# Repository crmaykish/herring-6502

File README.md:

# Herring 6502

Herring is an 8-bit computer built around the 65C02 CPU. It is designed as a backplane system. The backplane board is passive, providing only power, a reset switch, and system bus headers.
The system bus is exposed as single-row 40-pin female headers using standard 0.1 inch pin pitch.

## Hardware

The memory map is set up in the following way:

1. 0x0000 - 0x7FFF: Low RAM (32K)
2. 0x8000 - 0xBFFF: Bankable RAM (16K pages)
3. 0xC000 - 0xDFFF: Memory-mapped I/O (8K)
4. 0xE000 - 0xFFFF: ROM (8K)

Individual component boards are connected to the backplane via the 40-pin system bus. Most of the pins on the bus come directly from the 65C02 plus a few for peripheral support. They are mapped from left to right in the following order:

1. VCC (5v regulated)
2. GND
3. D0
4. D1
5. D2
6. D3
7. D4
8. D5
9. D6
10. D7
11. A0
12. A1
13. A2
14. A3
15. A4
16. A5
17. A6
18. A7
19. A8
20. A9
21. A10
22. A11
23. A12
24. A13
25. A14
26. A15
27. RESB - Reset (Active low)
28. CLK - System clock
29. RWB - Read/write flag (Read = high, Write = low)
30. IRQB - Interrupt request (Active low)
31. DEC0 - Functions as the RAM write-enable pin
32. DEC1 - Peripheral enable
33. DEC2 - Peripheral enable
34. DEC3 - Peripheral enable
35. DEC4 - Peripheral enable
36. DEC5 - Peripheral enable
37. DEC6 - Peripheral enable
38. DEC7 - Peripheral enable
39. BE - Bus Enable (Active high)
40. GND

## Software

Herring currently runs a simple monitor program from ROM that provides the basic peek, poke, jump commands as well as memory clearing and memory dumping. This monitor also functions as a bootloader, allowing new firmware to be copied into RAM from a host PC via serial port. I use a simple program on the PC to transfer firmware: https://github.com/crmaykish/ctt in this way.

All firmware development is done in C and uses the cc65 set of tools.

## Further Reading

See https://hackaday.io/project/181802-herring-6502-computer for project logs and more details on the hardware.

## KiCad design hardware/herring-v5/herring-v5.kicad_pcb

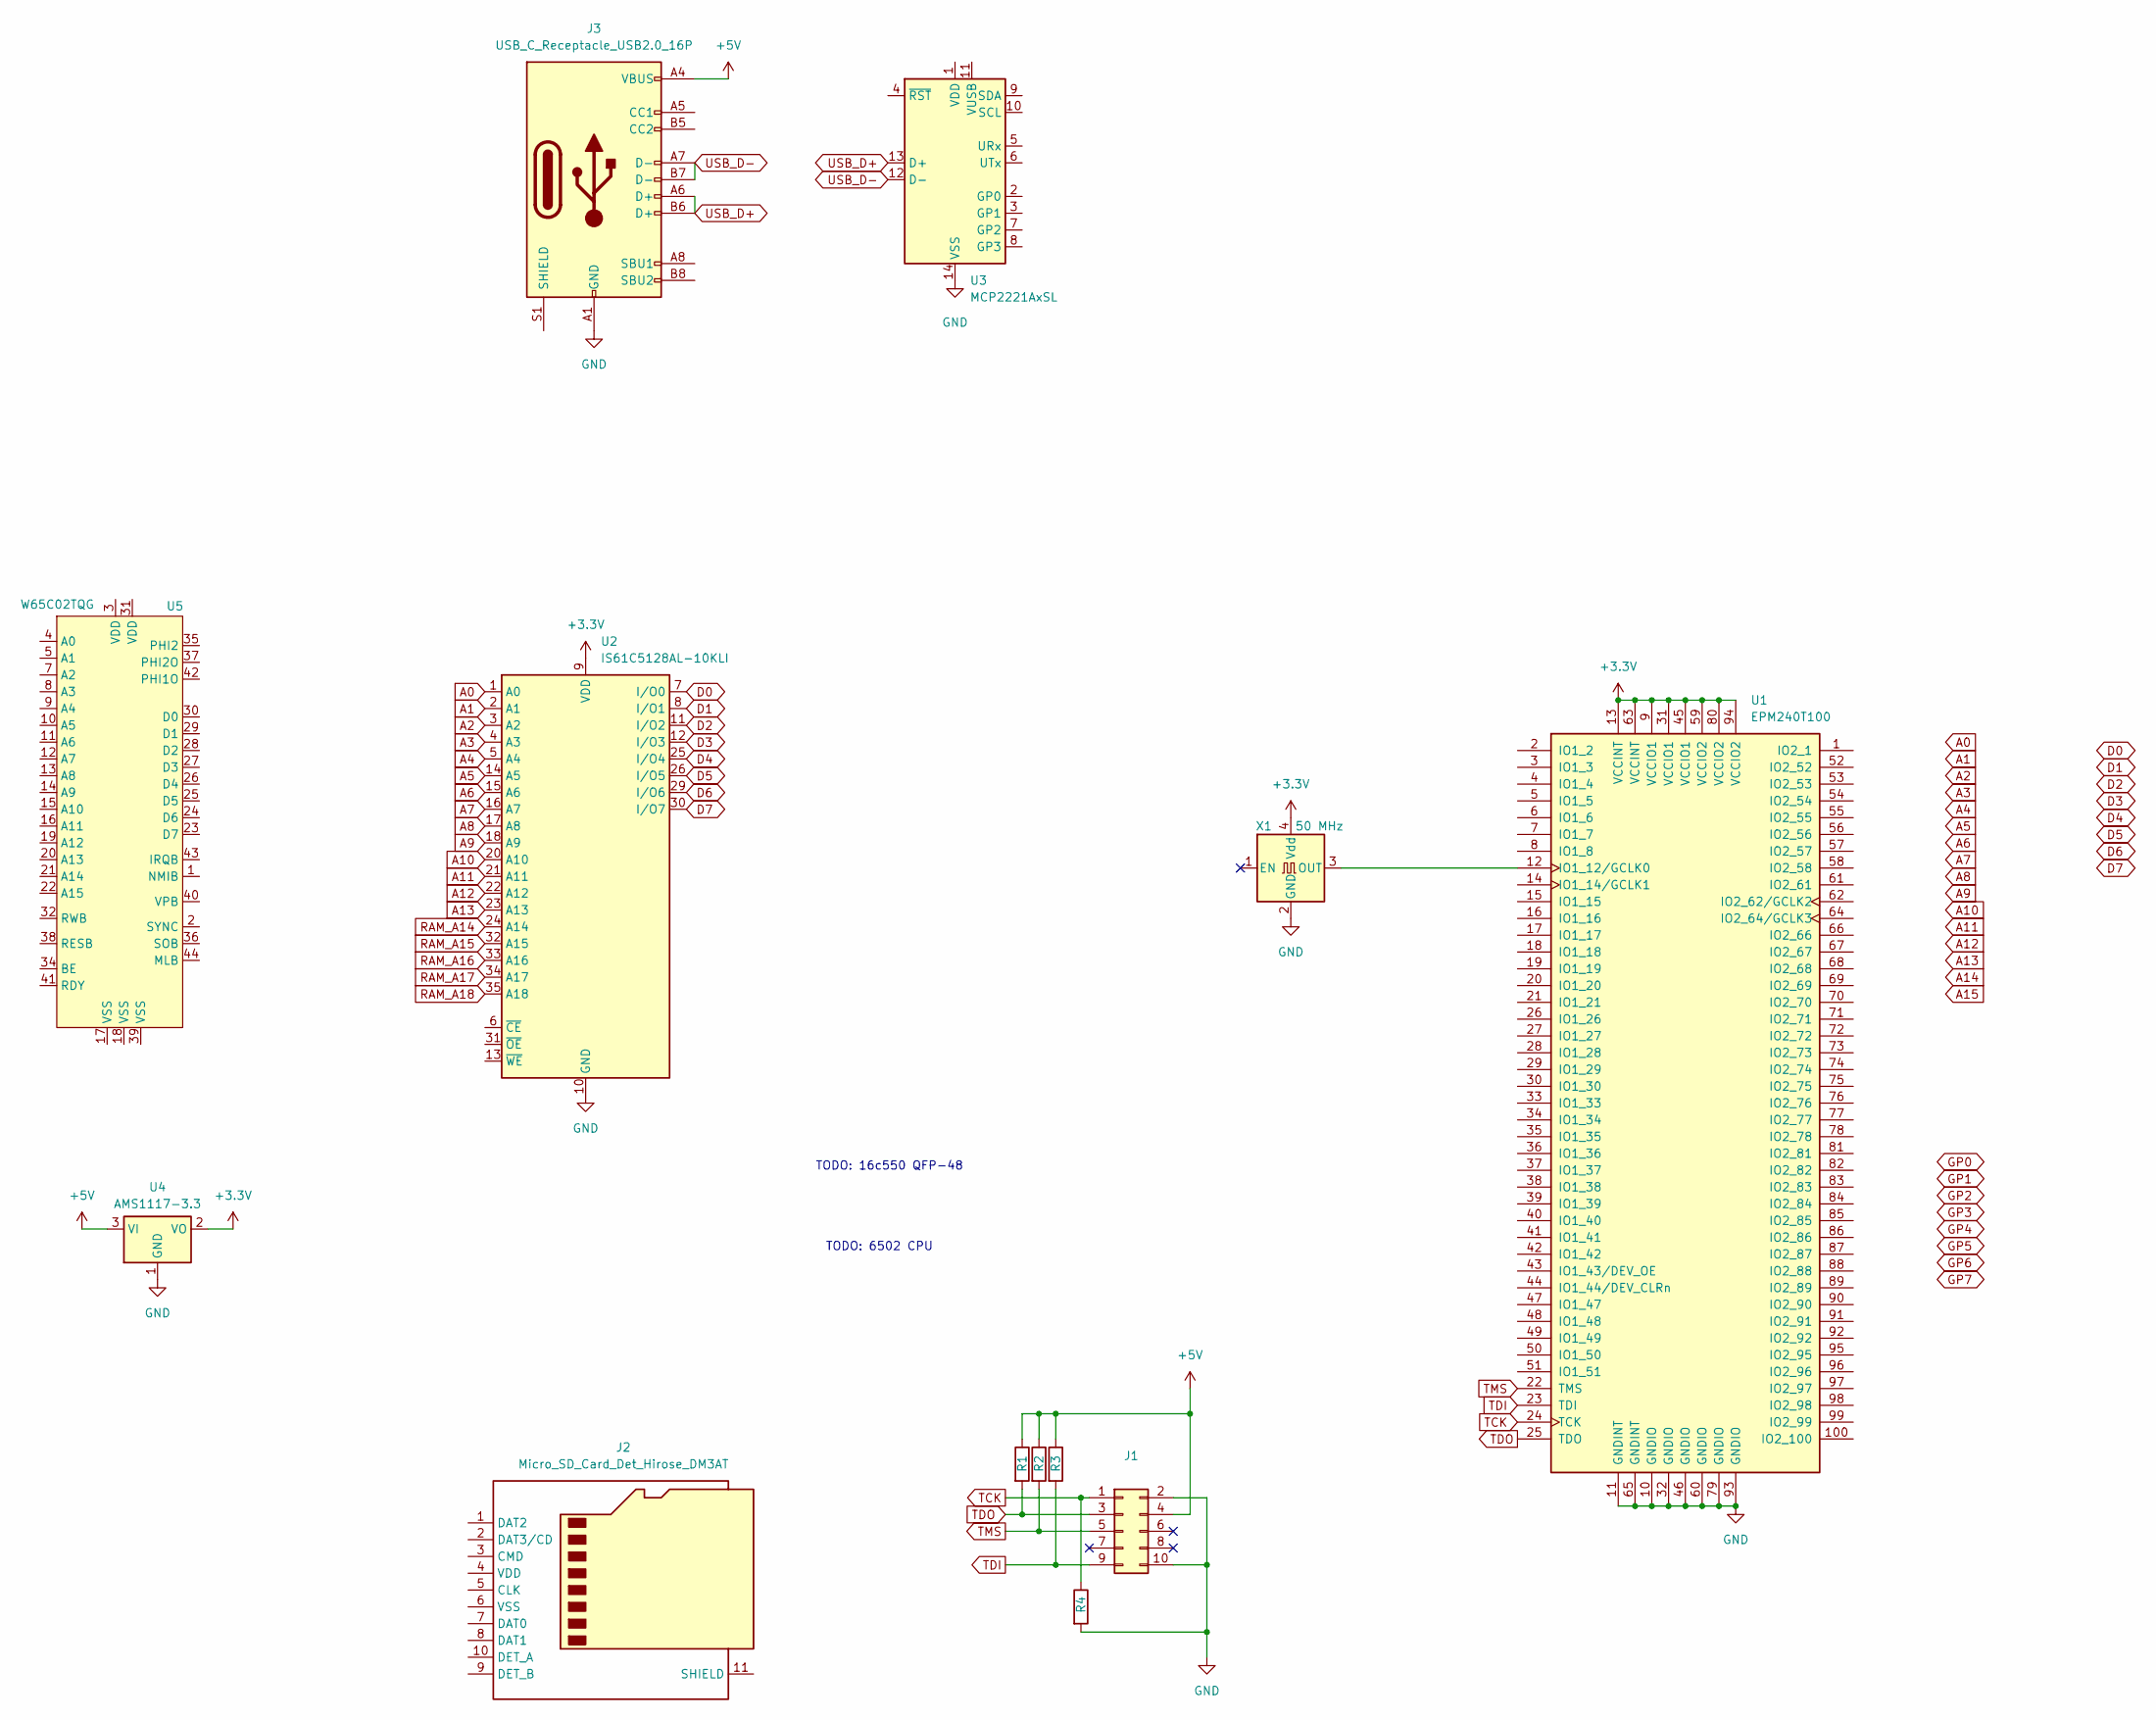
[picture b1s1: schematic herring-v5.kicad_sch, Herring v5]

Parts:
J1: Conn_02x05_Odd_Even; IDC-Header_2x05_P2.54mm_Vertical
J2: Micro_SD_Card_Det_Hirose_DM3AT; microSD_HC_Hirose_DM3AT-SF-PEJM5
J3: USB_C_Receptacle_USB2.0_16P; USB_C_Receptacle_GCT_USB4085
R1, R2, R3, R4: R; R_0805_2012Metric_Pad1.20x1.40mm_HandSolder
U1: EPM240T100; LQFP-100_14x14mm_P0.5mm
U2: IS61C5128AL-10KLI; SOJ-36_10.16x23.49mm_P1.27mm
U3: MCP2221AxSL; SOIC-14_3.9x8.7mm_P1.27mm
U4: AMS1117-3.3; SOT-223-3_TabPin2
U5: W65C02TQG; PQFP-44_10x10mm_P0.8mm
X1: 50 MHz; Oscillator_SMD_Abracon_ASV-4Pin_7.0x5.1mm

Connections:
+3.3V: U1.9 (VCCIO1), U1.13 (VCCINT), U1.31 (VCCIO1), U1.45 (VCCIO1), U1.59 (VCCIO2), U1.63 (VCCINT), U1.80 (VCCIO2), U1.94 (VCCIO2), U2.9 (VDD), U2.27 (VDD), U4.2 (VO), X1.4 (Vdd)
+5V: J1.4, J3.A4 (VBUS), J3.A9 (VBUS), J3.B4 (VBUS), J3.B9 (VBUS), R1.1, R2.1, R3.1, U4.3 (VI)
A0: U2.1 (A0)
A1: U2.2 (A1)
A2: U2.3 (A2)
A3: U2.4 (A3)
A4: U2.5 (A4)
A5: U2.14 (A5)
A6: U2.15 (A6)
A7: U2.16 (A7)
A8: U2.17 (A8)
A9: U2.18 (A9)
A10: U2.20 (A10)
A11: U2.21 (A11)
A12: U2.22 (A12)
A13: U2.23 (A13)
D0: U2.7 (I/O0)
D1: U2.8 (I/O1)
D2: U2.11 (I/O2)
D3: U2.12 (I/O3)
D4: U2.25 (I/O4)
D5: U2.26 (I/O5)
D6: U2.29 (I/O6)
D7: U2.30 (I/O7)
GND: J1.2, J1.10, J3.A1 (GND), J3.A12 (GND), J3.B1 (GND), J3.B12 (GND), R4.2, U1.10 (GNDIO), U1.11 (GNDINT), U1.32 (GNDIO), U1.46 (GNDIO), U1.60 (GNDIO), U1.65 (GNDINT), U1.79 (GNDIO), U1.93 (GNDIO), U2.10 (GND), U2.28 (GND), U3.14 (VSS), U4.1 (GND), X1.2 (GND)
unnamed: U1.12 (IO1_12/GCLK0), X1.3 (OUT)
RAM_A14: U2.24 (A14)
RAM_A15: U2.32 (A15)
RAM_A16: U2.33 (A16)
RAM_A17: U2.34 (A17)
RAM_A18: U2.35 (A18)
TCK: J1.1, R4.1, U1.24 (TCK)
TDI: J1.9, R3.2, U1.23 (TDI)
TDO: J1.3, R1.2, U1.25 (TDO)
TMS: J1.5, R2.2, U1.22 (TMS)
USB_D+: J3.A6 (D+), J3.B6 (D+), U3.13 (D+)
USB_D-: J3.A7 (D-), J3.B7 (D-), U3.12 (D-)

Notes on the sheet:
TODO: 16c550 QFP-48
TODO: 6502 CPU

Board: 2 copper layers, 13 parts (0 on the bottom side), 10 nets, no tracks yet.

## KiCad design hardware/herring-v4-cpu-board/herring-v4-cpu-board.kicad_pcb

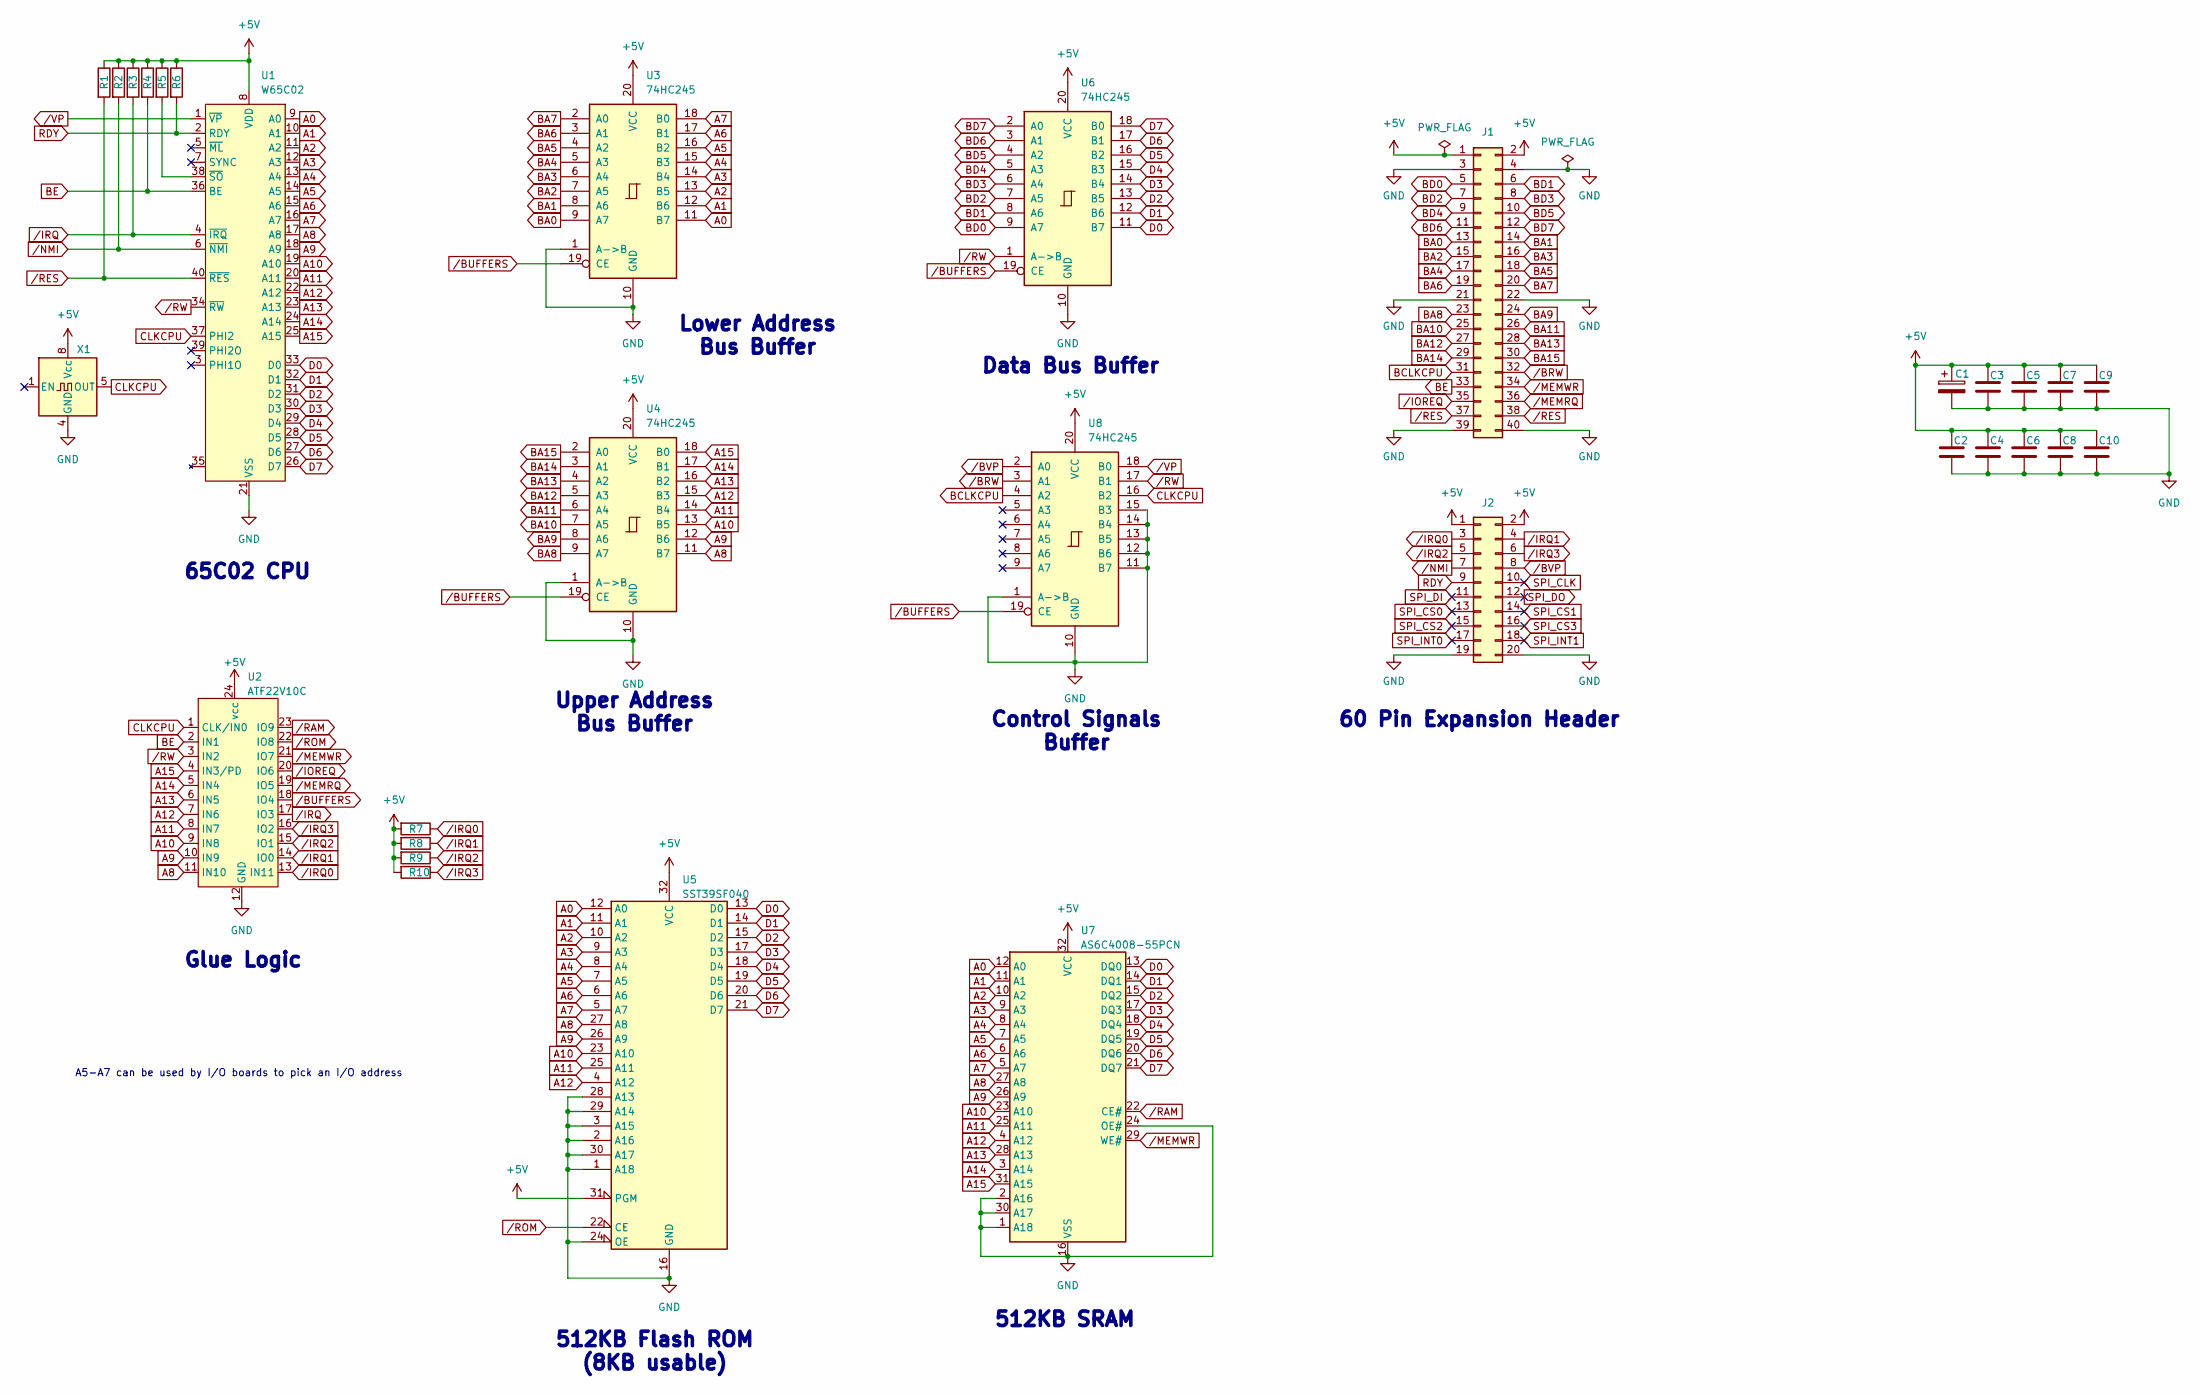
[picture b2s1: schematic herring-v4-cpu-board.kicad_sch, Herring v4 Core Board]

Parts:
C1: C_Polarized; CP_Radial_D10.0mm_P3.80mm
C2, C3, C4, C5, C6, C7, C8, C9, C10: C; C_Disc_D5.0mm_W2.5mm_P5.00mm
J1: Conn_02x20_Odd_Even; PinSocket_2x20_P2.54mm_Vertical
J2: Conn_02x10_Odd_Even; PinSocket_2x10_P2.54mm_Vertical
R1, R2, R3, R4, R5, R6, R7, R8, R9, R10: R; R_Axial_DIN0207_L6.3mm_D2.5mm_P7.62mm_Horizontal
U1: W65C02; DIP-40_W15.24mm
U2: ATF22V10C; DIP-24_W7.62mm
U3, U4, U6, U8: 74HC245; DIP-20_W7.62mm
U5: SST39SF040; DIP_Socket-32_W11.9_W12.7_W15.24_W17.78_W18.5_3M_232-1285-0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
U7: AS6C4008-55PCN; DIP-32_W15.24mm
X1: CXO_DIP8; Oscillator_DIP-8

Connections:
+5V: C1.1, C2.1, C3.1, C4.1, C5.1, C6.1, C7.1, C8.1, C9.1, C10.1, J1.1, J1.2, J2.1, J2.2, R1.1, R2.1, R3.1, R4.1, R5.1, R6.1, R7.2, R8.2, R9.2, R10.2, U1.8 (VDD), U2.24 (vcc), U3.20 (VCC), U4.20 (VCC), U5.31 (PGM), U5.32 (VCC), U6.20 (VCC), U7.32 (VCC), U8.20 (VCC), X1.8 (Vcc)
A0: U1.9 (A0), U3.11 (B7), U5.12 (A0), U7.12 (A0)
A1: U1.10 (A1), U3.12 (B6), U5.11 (A1), U7.11 (A1)
A2: U1.11 (A2), U3.13 (B5), U5.10 (A2), U7.10 (A2)
A3: U1.12 (A3), U3.14 (B4), U5.9 (A3), U7.9 (A3)
A4: U1.13 (A4), U3.15 (B3), U5.8 (A4), U7.8 (A4)
A5: U1.14 (A5), U3.16 (B2), U5.7 (A5), U7.7 (A5)
A6: U1.15 (A6), U3.17 (B1), U5.6 (A6), U7.6 (A6)
A7: U1.16 (A7), U3.18 (B0), U5.5 (A7), U7.5 (A7)
A8: U1.17 (A8), U2.11 (IN10), U4.11 (B7), U5.27 (A8), U7.27 (A8)
A9: U1.18 (A9), U2.10 (IN9), U4.12 (B6), U5.26 (A9), U7.26 (A9)
A10: U1.19 (A10), U2.9 (IN8), U4.13 (B5), U5.23 (A10), U7.23 (A10)
A11: U1.20 (A11), U2.8 (IN7), U4.14 (B4), U5.25 (A11), U7.25 (A11)
A12: U1.22 (A12), U2.7 (IN6), U4.15 (B3), U5.4 (A12), U7.4 (A12)
A13: U1.23 (A13), U2.6 (IN5), U4.16 (B2), U7.28 (A13)
A14: U1.24 (A14), U2.5 (IN4), U4.17 (B1), U7.3 (A14)
A15: U1.25 (A15), U2.4 (IN3/PD), U4.18 (B0), U7.31 (A15)
BA0: J1.13, U3.9 (A7)
BA1: J1.14, U3.8 (A6)
BA2: J1.15, U3.7 (A5)
BA3: J1.16, U3.6 (A4)
BA4: J1.17, U3.5 (A3)
BA5: J1.18, U3.4 (A2)
BA6: J1.19, U3.3 (A1)
BA7: J1.20, U3.2 (A0)
BA8: J1.23, U4.9 (A7)
BA9: J1.24, U4.8 (A6)
BA10: J1.25, U4.7 (A5)
BA11: J1.26, U4.6 (A4)
BA12: J1.27, U4.5 (A3)
BA13: J1.28, U4.4 (A2)
BA14: J1.29, U4.3 (A1)
BA15: J1.30, U4.2 (A0)
BCLKCPU: J1.31, U8.4 (A2)
BD0: J1.5, U6.9 (A7)
BD1: J1.6, U6.8 (A6)
BD2: J1.7, U6.7 (A5)
BD3: J1.8, U6.6 (A4)
BD4: J1.9, U6.5 (A3)
BD5: J1.10, U6.4 (A2)
BD6: J1.11, U6.3 (A1)
BD7: J1.12, U6.2 (A0)
BE: J1.33, R4.2, U1.36 (BE), U2.2 (IN1)
CLKCPU: U1.37 (PHI2), U2.1 (CLK/IN0), U8.16 (B2), X1.5 (OUT)
D0: U1.33 (D0), U5.13 (D0), U6.11 (B7), U7.13 (DQ0)
D1: U1.32 (D1), U5.14 (D1), U6.12 (B6), U7.14 (DQ1)
D2: U1.31 (D2), U5.15 (D2), U6.13 (B5), U7.15 (DQ2)
D3: U1.30 (D3), U5.17 (D3), U6.14 (B4), U7.17 (DQ3)
D4: U1.29 (D4), U5.18 (D4), U6.15 (B3), U7.18 (DQ4)
D5: U1.28 (D5), U5.19 (D5), U6.16 (B2), U7.19 (DQ5)
D6: U1.27 (D6), U5.20 (D6), U6.17 (B1), U7.20 (DQ6)
D7: U1.26 (D7), U5.21 (D7), U6.18 (B0), U7.21 (DQ7)
GND: C1.2, C2.2, C3.2, C4.2, C5.2, C6.2, C7.2, C8.2, C9.2, C10.2, J1.3, J1.4, J1.21, J1.22, J1.39, J1.40, J2.19, J2.20, U1.21 (VSS), U2.12 (GND), U3.1 (A->B), U3.10 (GND), U4.1 (A->B), U4.10 (GND), U5.1 (A18), U5.2 (A16), U5.3 (A15), U5.16 (GND), U5.24 (OE), U5.28 (A13), U5.29 (A14), U5.30 (A17), U6.10 (GND), U7.1 (A18), U7.2 (A16), U7.16 (VSS), U7.24 (OE#), U7.30 (A17), U8.1 (A->B), U8.10 (GND), U8.11 (B7), U8.12 (B6), U8.13 (B5), U8.14 (B4), U8.15 (B3), X1.4 (GND)
unnamed: R5.2, U1.38 (~SO)
RDY: J2.9, R6.2, U1.2 (RDY)
SPI_CLK: J2.10
SPI_CS0: J2.13
SPI_CS1: J2.14
SPI_CS2: J2.15
SPI_CS3: J2.16
SPI_DI: J2.11
SPI_DO: J2.12
SPI_INT0: J2.17
SPI_INT1: J2.18
/BRW: J1.32, U8.3 (A1)
/BUFFERS: U2.18 (IO4), U3.19 (CE), U4.19 (CE), U6.19 (CE), U8.19 (CE)
/BVP: J2.8, U8.2 (A0)
/IOREQ: J1.35, U2.20 (IO6)
/IRQ: R3.2, U1.4 (~IRQ), U2.17 (IO3)
/IRQ0: J2.3, R7.1, U2.13 (IN11)
/IRQ1: J2.4, R8.1, U2.14 (IO0)
/IRQ2: J2.5, R9.1, U2.15 (IO1)
/IRQ3: J2.6, R10.1, U2.16 (IO2)
/MEMRQ: J1.36, U2.19 (IO5)
/MEMWR: J1.34, U2.21 (IO7), U7.29 (WE#)
/NMI: J2.7, R2.2, U1.6 (~NMI)
/RAM: U2.23 (IO9), U7.22 (CE#)
/RES: J1.37, J1.38, R1.2, U1.40 (~RES)
/ROM: U2.22 (IO8), U5.22 (CE)
/RW: U1.34 (~RW), U2.3 (IN2), U6.1 (A->B), U8.17 (B1)
/VP: U1.1 (~VP), U8.18 (B0)

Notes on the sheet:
65C02 CPU
A5-A7 can be used by I/O boards to pick an I/O address
Glue Logic
Upper Address Bus Buffer
Control Signals Buffer
512KB SRAM
Lower Address Bus Buffer
512KB Flash ROM (8KB usable)
Data Bus Buffer
60 Pin Expansion Header

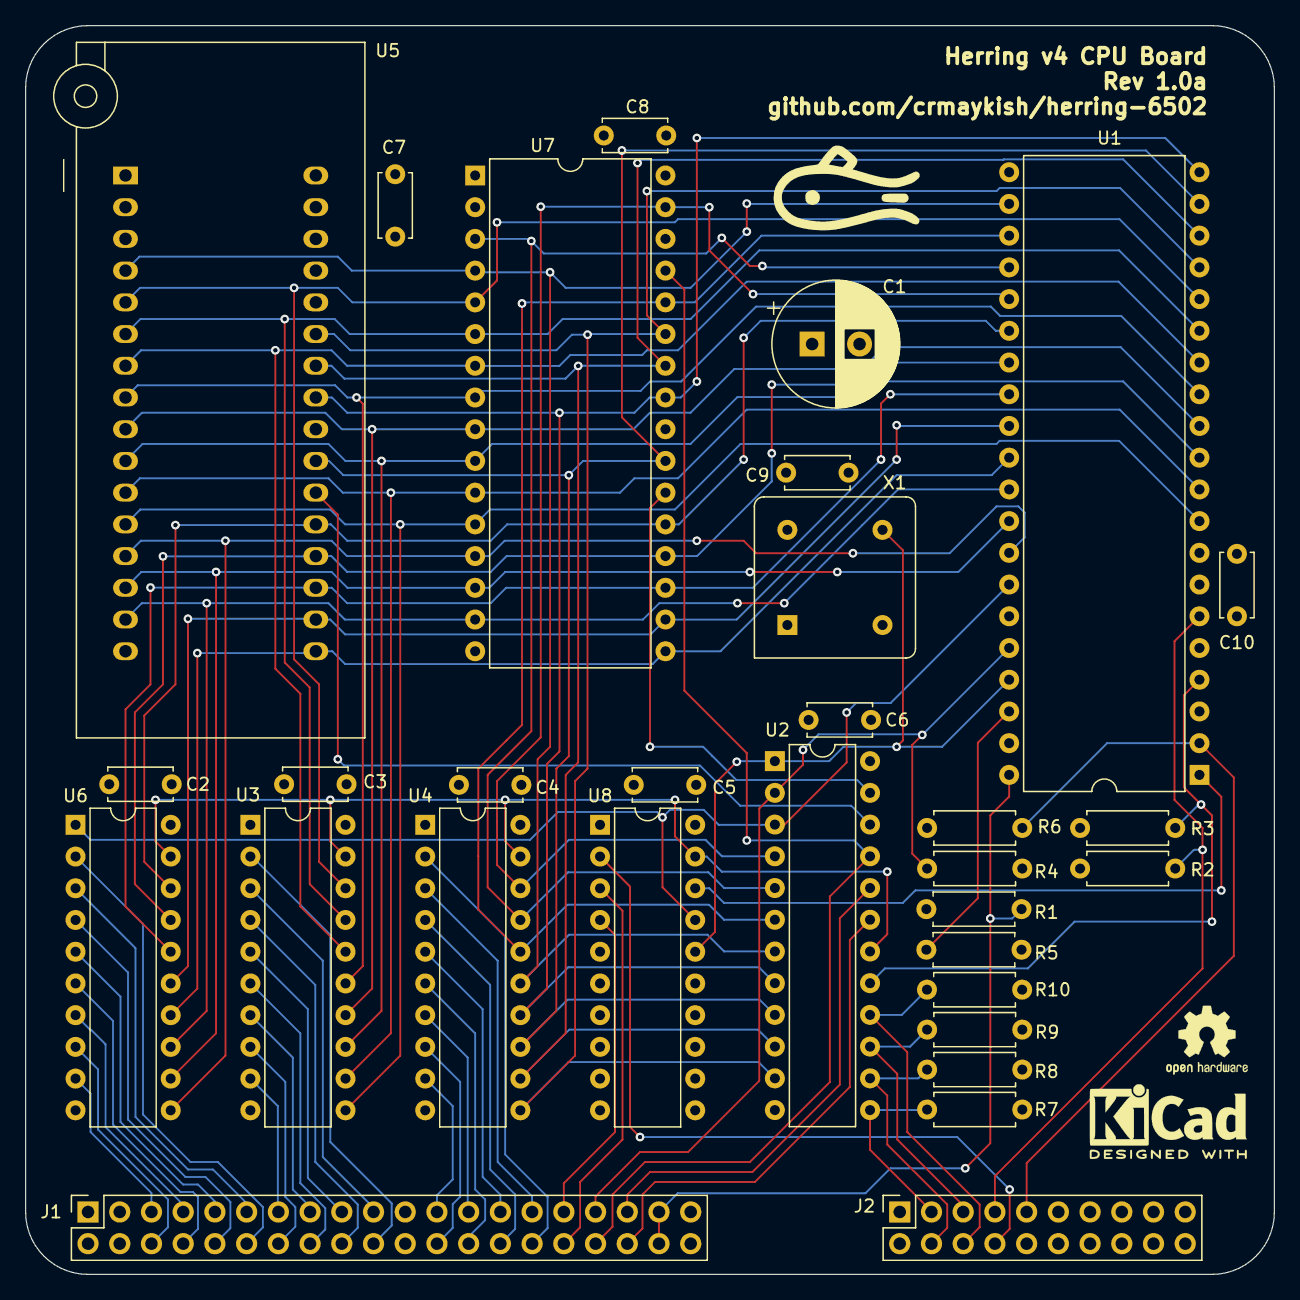
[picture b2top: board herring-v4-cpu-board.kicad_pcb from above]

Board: 4 copper layers, 100.0 x 100.0 mm, 31 parts (0 on the bottom side), 72 nets.

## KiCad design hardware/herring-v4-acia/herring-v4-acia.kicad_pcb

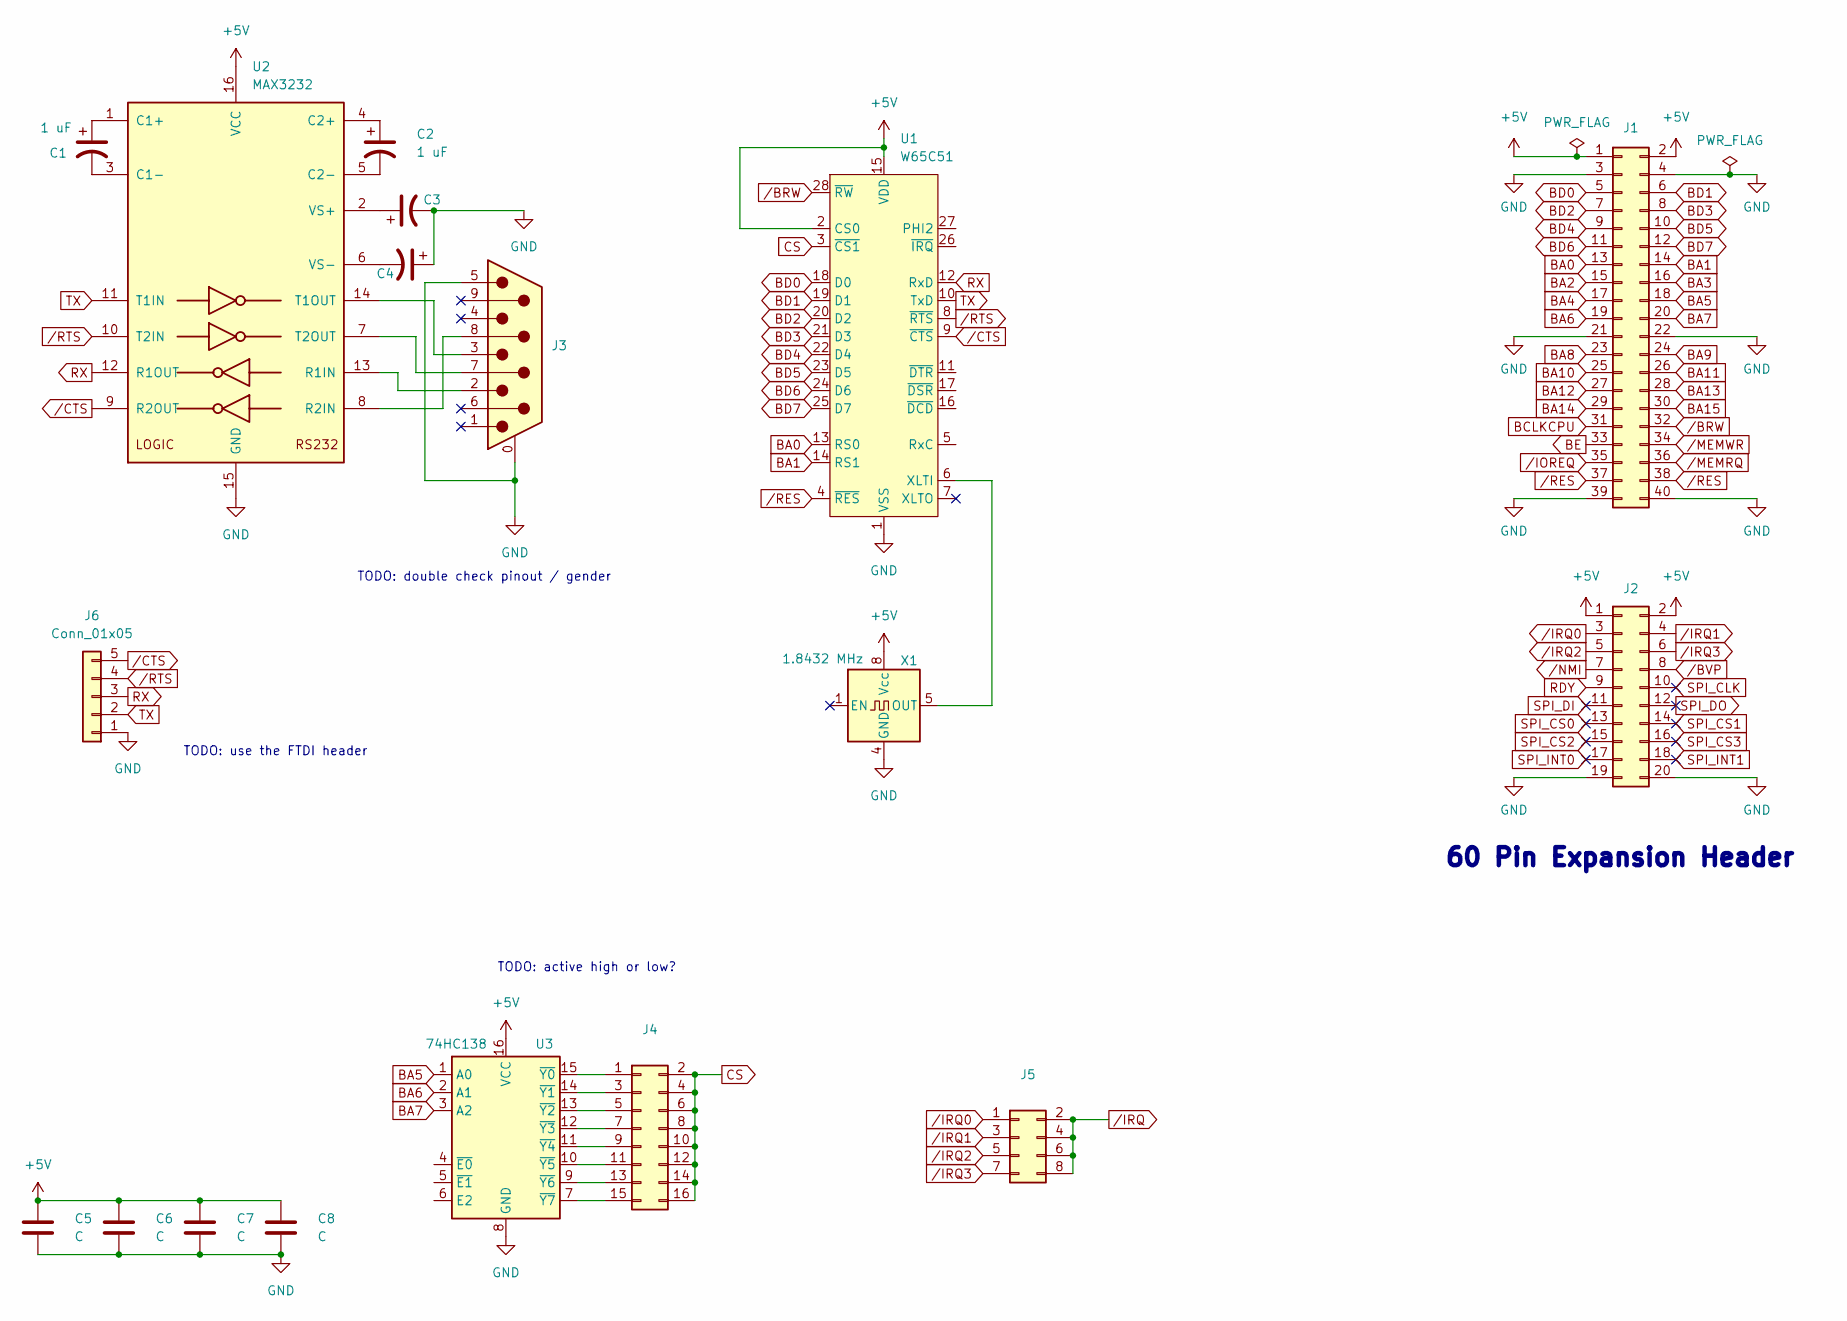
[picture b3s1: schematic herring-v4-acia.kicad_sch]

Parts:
C1, C2, C3: 1 uF; CP_Radial_D5.0mm_P2.50mm
C4: C_Polarized_US; CP_Radial_D5.0mm_P2.50mm
C5, C6, C7, C8: C; C_Disc_D4.3mm_W1.9mm_P5.00mm
J1: Conn_02x20_Odd_Even; PinSocket_2x20_P2.54mm_Vertical
J2: Conn_02x10_Odd_Even; PinSocket_2x10_P2.54mm_Vertical
J3: DE9_Plug_MountingHoles; DSUB-9_Male_Horizontal_P2.77x2.84mm_EdgePinOffset7.70mm_Hou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
J4: Conn_02x08_Odd_Even; PinHeader_2x08_P2.54mm_Vertical
J5: Conn_02x04_Odd_Even; PinHeader_2x04_P2.54mm_Vertical
J6: Conn_01x05; PinHeader_1x05_P2.54mm_Horizontal
U1: W65C51; DIP-28_W15.24mm
U2: MAX3232; DIP-16_W7.62mm
U3: 74HC138; DIP-16_W7.62mm
X1: 1.8432 MHz; Oscillator_DIP-8

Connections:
+5V: C5.1, C6.1, C7.1, C8.1, J1.1, J1.2, J2.1, J2.2, U1.2 (CS0), U1.15 (VDD), U2.16 (VCC), U3.16 (VCC), X1.8 (Vcc)
BA0: J1.13, U1.13 (RS0)
BA1: J1.14, U1.14 (RS1)
BA2: J1.15
BA3: J1.16
BA4: J1.17
BA5: J1.18, U3.1 (A0)
BA6: J1.19, U3.2 (A1)
BA7: J1.20, U3.3 (A2)
BA8: J1.23
BA9: J1.24
BA10: J1.25
BA11: J1.26
BA12: J1.27
BA13: J1.28
BA14: J1.29
BA15: J1.30
BCLKCPU: J1.31
BD0: J1.5, U1.18 (D0)
BD1: J1.6, U1.19 (D1)
BD2: J1.7, U1.20 (D2)
BD3: J1.8, U1.21 (D3)
BD4: J1.9, U1.22 (D4)
BD5: J1.10, U1.23 (D5)
BD6: J1.11, U1.24 (D6)
BD7: J1.12, U1.25 (D7)
BE: J1.33
CS: J4.2, J4.4, J4.6, J4.8, J4.10, J4.12, J4.14, J4.16, U1.3 (~CS1)
GND: C3.2, C4.1, C5.2, C6.2, C7.2, C8.2, J1.3, J1.4, J1.21, J1.22, J1.39, J1.40, J2.19, J2.20, J3.0 (PAD), J3.5, J6.1, U1.1 (VSS), U2.15 (GND), U3.8 (GND), X1.4 (GND)
unnamed: J4.1, U3.15 (~Y0)
unnamed: J4.3, U3.14 (~Y1)
unnamed: J4.5, U3.13 (~Y2)
unnamed: J4.7, U3.12 (~Y3)
unnamed: J4.9, U3.11 (~Y4)
unnamed: J4.11, U3.10 (~Y5)
unnamed: J4.13, U3.9 (~Y6)
unnamed: J4.15, U3.7 (~Y7)
unnamed: U1.6 (XLTI), X1.5 (OUT)
unnamed: C1.1, U2.1 (C1+)
unnamed: C1.2, U2.3 (C1-)
unnamed: C2.1, U2.4 (C2+)
unnamed: C2.2, U2.5 (C2-)
unnamed: J3.2, U2.13 (R1IN)
unnamed: J3.8, U2.8 (R2IN)
unnamed: J3.3, U2.14 (T1OUT)
unnamed: J3.7, U2.7 (T2OUT)
unnamed: C3.1, U2.2 (VS+)
unnamed: C4.2, U2.6 (VS-)
RDY: J2.9
RX: J6.3, U1.12 (RxD), U2.12 (R1OUT)
SPI_CLK: J2.10
SPI_CS0: J2.13
SPI_CS1: J2.14
SPI_CS2: J2.15
SPI_CS3: J2.16
SPI_DI: J2.11
SPI_DO: J2.12
SPI_INT0: J2.17
SPI_INT1: J2.18
TX: J6.2, U1.10 (TxD), U2.11 (T1IN)
/BRW: J1.32, U1.28 (~RW)
/BVP: J2.8
/CTS: J6.5, U1.9 (~CTS), U2.9 (R2OUT)
/IOREQ: J1.35
/IRQ: J5.2, J5.4, J5.6, J5.8
/IRQ0: J2.3, J5.1
/IRQ1: J2.4, J5.3
/IRQ2: J2.5, J5.5
/IRQ3: J2.6, J5.7
/MEMRQ: J1.36
/MEMWR: J1.34
/NMI: J2.7
/RES: J1.37, J1.38, U1.4 (~RES)
/RTS: J6.4, U1.8 (~RTS), U2.10 (T2IN)

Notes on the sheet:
TODO: use the FTDI header
TODO: active high or low?
TODO: double check pinout / gender
60 Pin Expansion Header

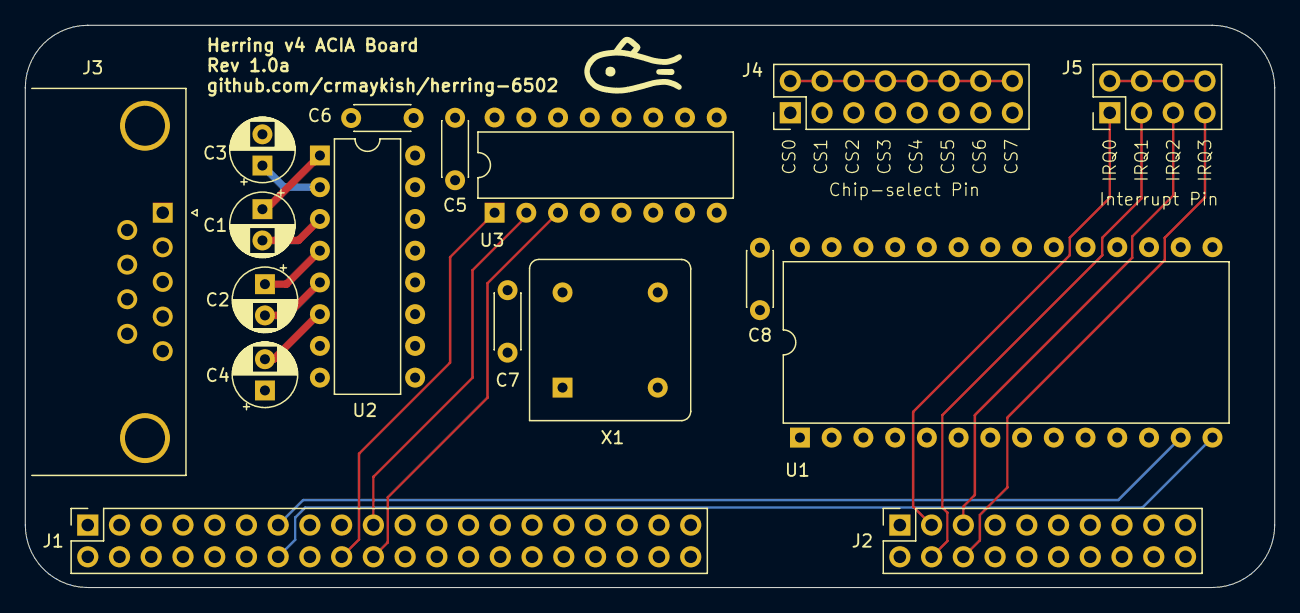
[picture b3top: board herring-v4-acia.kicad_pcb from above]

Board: 2 copper layers, 100.0 x 45.0 mm, 17 parts (0 on the bottom side), 46 nets.

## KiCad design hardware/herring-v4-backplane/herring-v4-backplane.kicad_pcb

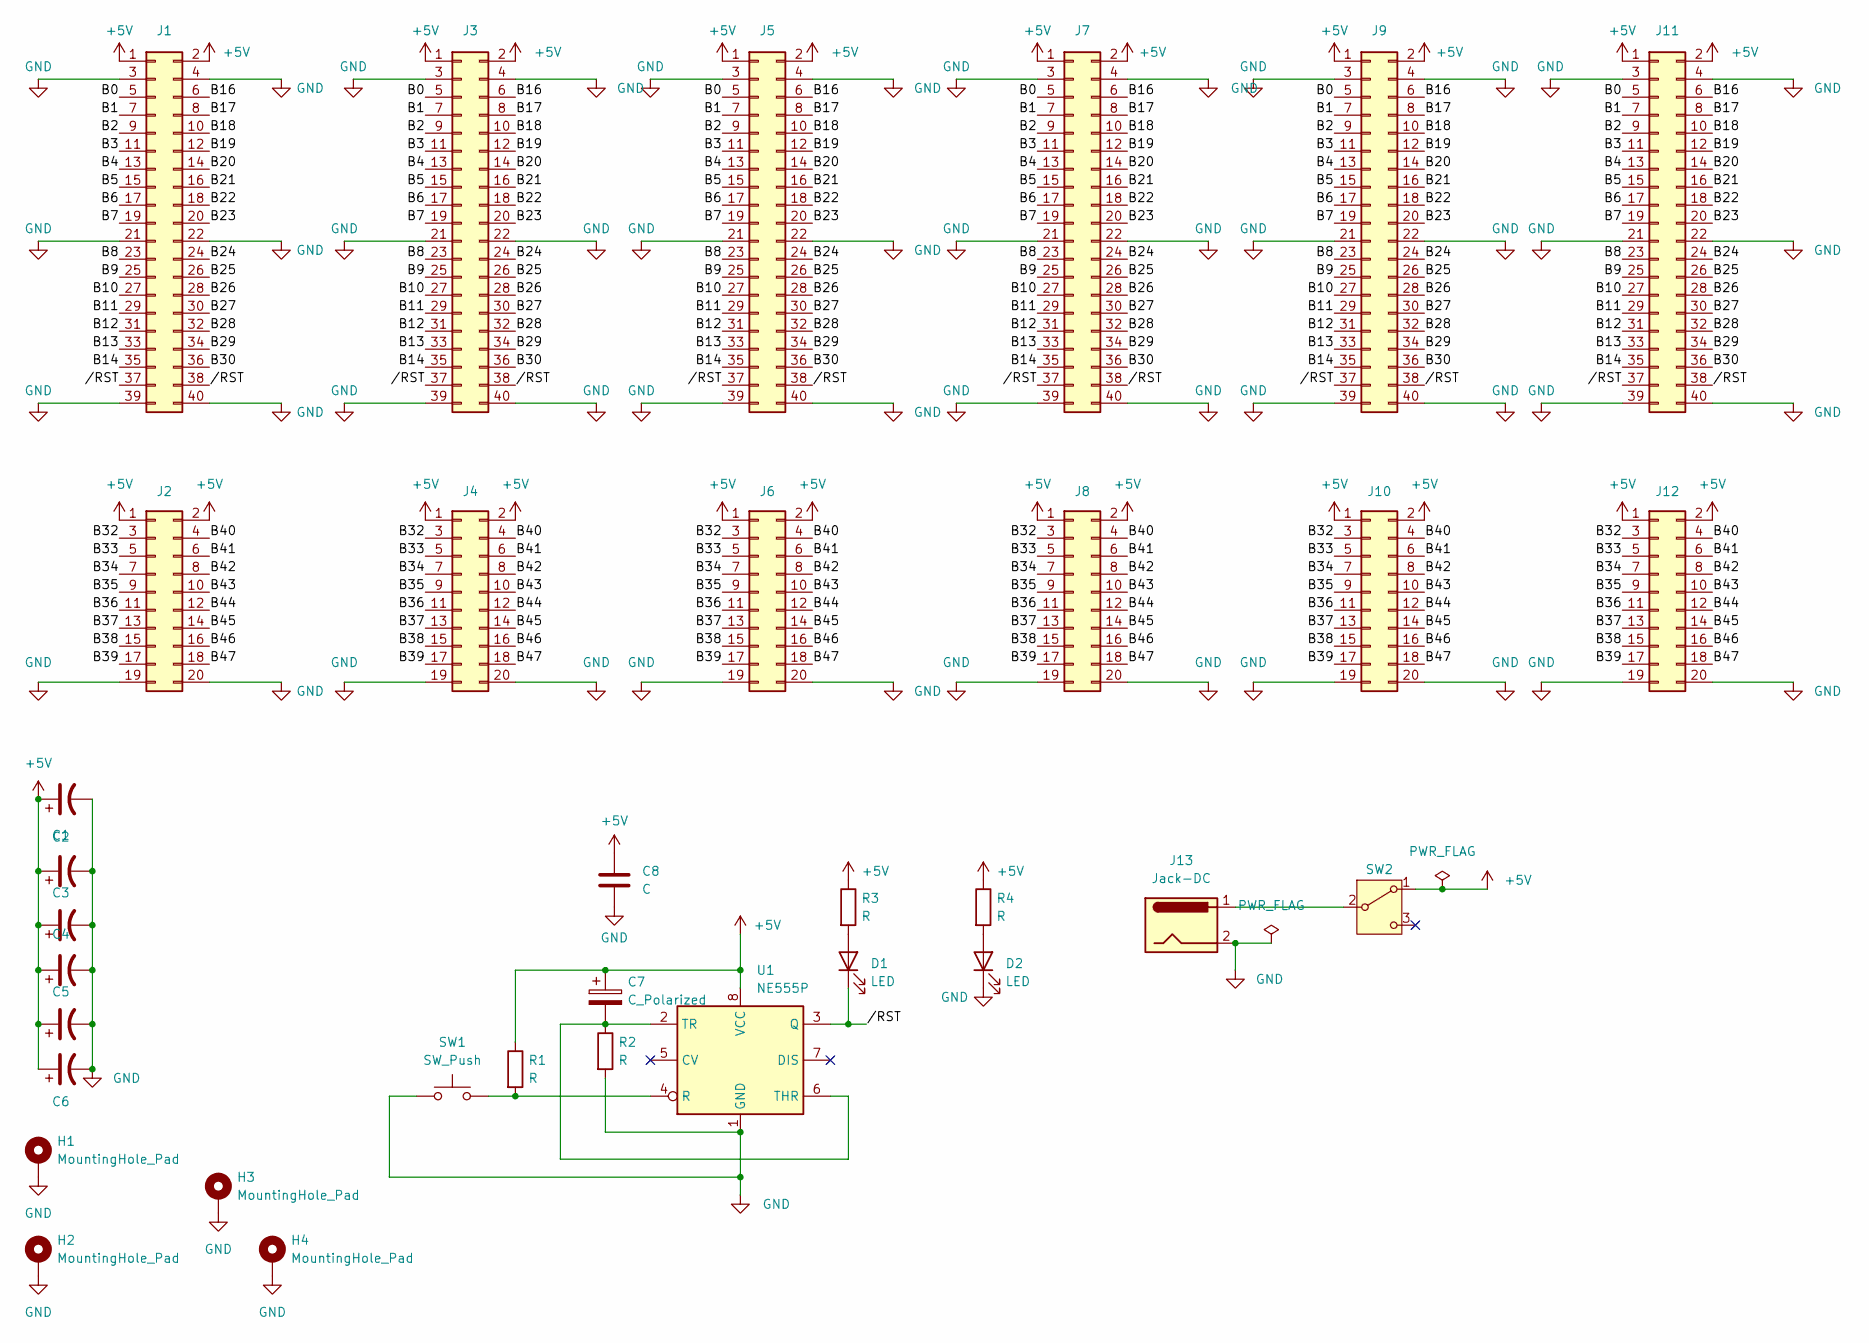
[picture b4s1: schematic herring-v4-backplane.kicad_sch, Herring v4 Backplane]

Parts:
C1: C_Polarized_US; CP_Radial_D8.0mm_P3.80mm
C2, C3, C4, C5, C6: C_Polarized_US; CP_Radial_D5.0mm_P2.50mm
C7: C_Polarized; CP_Radial_D5.0mm_P2.50mm
C8: C; C_Disc_D4.3mm_W1.9mm_P5.00mm
D1, D2: LED; LED_D5.0mm
H1, H2, H3, H4: MountingHole_Pad; MountingHole_3.2mm_M3_Pad
J1, J3, J5, J7, J9, J11: Conn_02x20_Odd_Even; PinSocket_2x20_P2.54mm_Vertical
J2, J4, J6, J8, J10, J12: Conn_02x10_Odd_Even; PinSocket_2x10_P2.54mm_Vertical
J13: Jack-DC; BarrelJack_Kycon_KLDX-0202-xC_Horizontal
R1, R2, R3, R4: R; R_Axial_DIN0207_L6.3mm_D2.5mm_P7.62mm_Horizontal
SW1: SW_Push; SW_PUSH_6mm_H5mm
SW2: SW_SPDT; SW_Mini_Toggle
U1: NE555P; DIP-8_W7.62mm

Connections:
+5V: C1.1, C2.1, C3.1, C4.1, C5.1, C6.1, C7.1, C8.1, J1.1, J1.2, J2.1, J2.2, J3.1, J3.2, J4.1, J4.2, J5.1, J5.2, J6.1, J6.2, J7.1, J7.2, J8.1, J8.2, J9.1, J9.2, J10.1, J10.2, J11.1, J11.2, J12.1, J12.2, R1.1, R3.1, R4.1, SW2.1 (A), U1.8 (VCC)
/B0: J1.5, J3.5, J5.5, J7.5, J9.5, J11.5
/B1: J1.7, J3.7, J5.7, J7.7, J9.7, J11.7
/B2: J1.9, J3.9, J5.9, J7.9, J9.9, J11.9
/B3: J1.11, J3.11, J5.11, J7.11, J9.11, J11.11
/B4: J1.13, J3.13, J5.13, J7.13, J9.13, J11.13
/B5: J1.15, J3.15, J5.15, J7.15, J9.15, J11.15
/B6: J1.17, J3.17, J5.17, J7.17, J9.17, J11.17
/B7: J1.19, J3.19, J5.19, J7.19, J9.19, J11.19
/B8: J1.23, J3.23, J5.23, J7.23, J9.23, J11.23
/B9: J1.25, J3.25, J5.25, J7.25, J9.25, J11.25
/B10: J1.27, J3.27, J5.27, J7.27, J9.27, J11.27
/B11: J1.29, J3.29, J5.29, J7.29, J9.29, J11.29
/B12: J1.31, J3.31, J5.31, J7.31, J9.31, J11.31
/B13: J1.33, J3.33, J5.33, J7.33, J9.33, J11.33
/B14: J1.35, J3.35, J5.35, J7.35, J9.35, J11.35
/B16: J1.6, J3.6, J5.6, J7.6, J9.6, J11.6
/B17: J1.8, J3.8, J5.8, J7.8, J9.8, J11.8
/B18: J1.10, J3.10, J5.10, J7.10, J9.10, J11.10
/B19: J1.12, J3.12, J5.12, J7.12, J9.12, J11.12
/B20: J1.14, J3.14, J5.14, J7.14, J9.14, J11.14
/B21: J1.16, J3.16, J5.16, J7.16, J9.16, J11.16
/B22: J1.18, J3.18, J5.18, J7.18, J9.18, J11.18
/B23: J1.20, J3.20, J5.20, J7.20, J9.20, J11.20
/B24: J1.24, J3.24, J5.24, J7.24, J9.24, J11.24
/B25: J1.26, J3.26, J5.26, J7.26, J9.26, J11.26
/B26: J1.28, J3.28, J5.28, J7.28, J9.28, J11.28
/B27: J1.30, J3.30, J5.30, J7.30, J9.30, J11.30
/B28: J1.32, J3.32, J5.32, J7.32, J9.32, J11.32
/B29: J1.34, J3.34, J5.34, J7.34, J9.34, J11.34
/B30: J1.36, J3.36, J5.36, J7.36, J9.36, J11.36
/B32: J2.3, J4.3, J6.3, J8.3, J10.3, J12.3
/B33: J2.5, J4.5, J6.5, J8.5, J10.5, J12.5
/B34: J2.7, J4.7, J6.7, J8.7, J10.7, J12.7
/B35: J2.9, J4.9, J6.9, J8.9, J10.9, J12.9
/B36: J2.11, J4.11, J6.11, J8.11, J10.11, J12.11
/B37: J2.13, J4.13, J6.13, J8.13, J10.13, J12.13
/B38: J2.15, J4.15, J6.15, J8.15, J10.15, J12.15
/B39: J2.17, J4.17, J6.17, J8.17, J10.17, J12.17
/B40: J2.4, J4.4, J6.4, J8.4, J10.4, J12.4
/B41: J2.6, J4.6, J6.6, J8.6, J10.6, J12.6
/B42: J2.8, J4.8, J6.8, J8.8, J10.8, J12.8
/B43: J2.10, J4.10, J6.10, J8.10, J10.10, J12.10
/B44: J2.12, J4.12, J6.12, J8.12, J10.12, J12.12
/B45: J2.14, J4.14, J6.14, J8.14, J10.14, J12.14
/B46: J2.16, J4.16, J6.16, J8.16, J10.16, J12.16
/B47: J2.18, J4.18, J6.18, J8.18, J10.18, J12.18
//RST: D1.1 (K), J1.37, J1.38, J3.37, J3.38, J5.37, J5.38, J7.37, J7.38, J9.37, J9.38, J11.37, J11.38, U1.3 (Q)
GND: C1.2, C2.2, C3.2, C4.2, C5.2, C6.2, C8.2, D2.1 (K), H1.1, H2.1, H3.1, H4.1, J1.3, J1.4, J1.21, J1.22, J1.39, J1.40, J2.19, J2.20, J3.3, J3.4, J3.21, J3.22, J3.39, J3.40, J4.19, J4.20, J5.3, J5.4, J5.21, J5.22, J5.39, J5.40, J6.19, J6.20, J7.3, J7.4, J7.21, J7.22, J7.39, J7.40, J8.19, J8.20, J9.3, J9.4, J9.21, J9.22, J9.39, J9.40, J10.19, J10.20, J11.3, J11.4, J11.21, J11.22, J11.39, J11.40, J12.19, J12.20, J13.2, R2.2, SW1.1, U1.1 (GND)
unnamed: D1.2 (A), R3.2
unnamed: D2.2 (A), R4.2
unnamed: J13.1, SW2.2 (B)
unnamed: R1.2, SW1.2, U1.4 (R)
unnamed: C7.2, R2.1, U1.2 (TR), U1.6 (THR)
